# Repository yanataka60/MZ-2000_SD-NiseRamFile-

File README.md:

# MZ-2000_SD+偽RAMFILE複合ボード

しっぽいいんちょさんが作られた「偽RAMFILE for MZ-1500」を元にしてMZ-2000用にVRAM、GRAMのエミュレートの追加及びMZ-2000_SDと合体させたボードです。

以下の機能があります。

・MZ-2000_SDの起動及びMZ-2000_SDの機能

・EMM1からの起動(ただし、EMM1にHu-BASICの起動ディスクイメージがある場合のみ)

・MZ-2000のテキスト出力及びグラフィック出力をエミュレートしてVGA出力

・EMM1エミュレータ(320KByte)

・漢字ROMボードエミュレータ

・VGA出力される出力をI/Oポートの操作により機能強化(主にテキスト関連)

　　・キャラクタ単位でFONTの変更

　　・FONTキャラクタごとの色(前景色)及び背景色の指定

　　・すべてのキャラクタを1Dot単位で色指定可能なPCG

　　・FONTとPCGのプライオリティ設定

　　・テキストの色パレット機能

　　・グラフィックの色パレット機能

　　・テキストとグラフィックを色ごとにプライオリティ設定

MZ-2000_SD: https://github.com/yanataka60/MZ-2000_SD

#### アップロード済みのuf2ファイルでの正常動作が確認されました。当方ではSourceからの再ビルドにおいても問題は発生していません。
~~#### 2026.3.5追記 VGA出力はかなりシビアなタイミングになっています。グラフィックスを使いこなしたアクションゲームの中にはVGA出力が追いつかずに正常に表示されないものもあるようです。~~

## 回路図
　KiCadフォルダ内のMZ-2000_SD+NRF.pdfを参照してください。

[回路図](https://github.com/yanataka60/MZ-2000_SD-NiseRamFile-/blob/main/Kiacd/MZ-2000_SD%2BNRF.pdf)

|番号|品名|数量|備考|
| ------------ | ------------ | ------------ | ------------ |
|J2,J3|ピンソケット2x15Pin|2|RP2350Bマイコンボード用,秋月電子通商 FHU-2x42SGなど|
|J4|VGA用基板ソケット 3列15ピン|1|マルツ DJ-VGA14.5など (注1)|
||J5、J6のいずれか|||
|J5|Micro_SD_Card_Kit|1|秋月電子通商 AE-microSD-LLCNV (注2)|
|J6|MicroSD Card Adapter|1|Arduino等に使われる5V電源に対応したもの(注4)|
|U1|74LS04|1||
|U2|74LS30|1||
|U3|8255|1||
|U4|Arduino_Pro_Mini_5V|1|Atmega328版を使用 168版は不可。(注3)|
||RP2350Bボード(Raspberry Pi Pico 2)|1|Amazon WA00021 RP2350Bマイコンボードなど|
|C1-C3|積層セラミックコンデンサ 0.1uF|3||
|C4|電解コンデンサ 16v100uF|1||
|D1|ダイオード 1N5819|1||
|R1-R3|カーボン抵抗 330Ω|3||
||ピンヘッダ|2Pin分|Arduino_Pro_MiniにはA4、A5用のピンヘッダが付いていないため別途調達が必要です 秋月電子通商 PH-1x40SGなど|
||ピンソケット(任意)|26Pin分|Arduino_Pro_Miniを取り外し可能としたい場合に調達します 秋月電子通商 FHU-1x42SGなど|

　　　注1)VGA用基板ソケットには、ピン間隔の異なるものがあるようです。マルツ DJ-VGA14.5ではないものを購入する場合はこちらで寸法を確認してください。

　　　https://www.marutsu.co.jp/contents/shop/marutsu/datasheet/DJ-VGA14.5.pdf

　　　注2)秋月電子通商　AE-microSD-LLCNVのJ1ジャンパはショートしてください。

　　　注3)Arduino Pro MiniはA4、A5ピンも使っています。

　　　注4)MicroSD Card Adapterを使う場合

　　　　　J6に取り付けます。

MicroSD Card Adapterについているピンヘッダを除去してハンダ付けするのが一番確実ですが、J6の穴にMicroSD Card Adapterをぴったりと押しつけ、裏から多めにハンダを流し込むことでハンダ付けをする方法もあります。なお、この方法の時にはしっかりハンダ付けが出来たかテスターで導通を確認しておいた方が安心です。

ハンダ付けに自信のない方はJ5の秋月電子通商　AE-microSD-LLCNVをお使いください。AE-microSD-LLCNVならパワーLED、アクセスLEDが付いています。

## 偽RAMFILE for MZ-2000の書込み
　RP2350Bフォルダにあるniseramfile.uf2をRP2350Bマイコンボードに書き込みます。

　RP2350BのBOOTボタンを押しながらUSB-Cケーブルを接続するとパソコンがUSBメディアとして認識しますのでniseramfile.uf2をドロップすると自動的に書き込まれます。

　書き込みが終了するとパソコンからはUSBとして見えなくなりますのでそうなったらケーブルを抜いて終了です。

## MZ-2000_SD BOOT PROGRAMをMZ-1R12 SRAMメモリ 0番バックアップスロットへ書き込み
　MZ-2000_SDリポジトリEMMフォルダ内のBOOT_A_LOADER.binをMZ-1R12 SRAMメモリ 0番バックアップスロットへ書き込んでください。

https://github.com/yanataka60/MZ-2000_SD/blob/main/EMM/BOOT_A_LOADER.bin

　書き込みにはpicotool.exeが必要となります。以下のウェブページ右側の「Releases」からダウンロードできます。

https://github.com/raspberrypi/pico-sdk-tools

```
picotool.exe load -v -x BOOT_A_LOADER.bin  -t bin -o 0x10080000
```

　次にSDカードに「@BOOT-A MZ-2000.bin」を置きます。作成方法は、MZ-2000_SDを参照してください。

https://github.com/yanataka60/MZ-2000_SD?tab=readme-ov-file#boot-a-mz-xxxxbin%E3%82%92%E4%BD%9C%E6%88%90%E3%81%97%E3%81%A6sd-card%E3%81%AB%E4%BF%9D%E5%AD%98%E3%81%99%E3%82%8B

　また、EMM1に起動可能な内容(HuBASIC起動イメージ)があればEMMからの起動が可能です。

　EMMの内容をチェックしていないのでEMMが起動可能な内容(HuBASIC起動イメージ)でなかった場合には暴走しますのでご注意ください。

　EMMから起動するためには、MZ-2000_SDリポジトリEMMフォルダ内の「@BOOT-EMM1.MZT」をSDカードにコピーしておく必要があります。

　EMM1からの起動方法は、「/」キーとテンキーの「1」を同時に押しながら電源ON時又はIPLリセットすることで「EMM1」のHuBASICから起動させることが出来ます。

## FONTファイルの書込み
　VGA出力を有効とするためにはMZ-2000のフォントをRP2350Bに書き込む必要があります。

　MZ-2000はソフトウェア的にフォントを取り出すすべがありません。頑張って作ってください。

　私はオーナーズマニュアルのASCIIコード表を見ながら作成しました。

　書き込みはpicotoolを使います。

```
picotool.exe load -v -x font.rom  -t bin -o 0x1001f000
```

## Arduinoプログラム
　MZ-2000_SDを参照してください。

https://github.com/yanataka60/MZ-2000_SD?tab=readme-ov-file#arduino%E3%83%97%E3%83%AD%E3%82%B0%E3%83%A9%E3%83%A0-1

## 拡張機能の使い方
### MZ-2000_SDの起動
　MZ-2000_SDの起動方法と同じです。「/」キーを押しながら電源投入又はIPL RESETしてください。

### EMM1エミュレータ
　320KByteのEMM1として機能します。バッテリーバックアップ機能はなく、電源断で内容は消失します。

　ただし、バックアップ用のSlotが32個用意されているので電源断前にSlotに退避しておくことが可能です。

　また、Slot0の内容は電源投入又はIPL RESETした時にEMM1に自動的にコピーされるのであたかもバッテリーバックアップされていたかのような使い方が出来ます。

　EMMとSlotとのやり取りはI/Oポートから指示します。

#### SlotxxからEMM1への復帰
|アドレス|R/W|説明|
| ------------ | ------------ | ------------ |
|8Ch|W|指定したSlot番号(0～31)のSlotの内容をEMM1に復帰|

#### EMM1からSlotxxへの退避
|アドレス|R/W|説明|
| ------------ | ------------ | ------------ |
|8Dh|W|指定したSlot番号(0～31)のSlotへEMM1の内容を退避|

HuBASICからは以下のようになります。

```
OUT &H8C,0
```

```
OUT &H8D,0
```

　また、EMM1に起動可能な内容(HuBASIC起動イメージ)があればEMMからの起動が可能です。

　EMMの内容をチェックしていないのでEMMが起動可能な内容(HuBASIC起動イメージ)でなかった場合には暴走しますのでご注意ください。

　EMM1からの起動方法は、「/」キーとテンキーの「1」を同時に押しながら電源ON時又はIPLリセットすることで「EMM1」のHuBASICから起動させることが出来ます。

　EMM1へのHuBASIC起動ディスクイメージ作成は、DISK版HuBASICのUtilityからEMM1へのCOPY ALLで作ってください。

　また、Emulatorで作られたEMMイメージを登録する場合はpicotoolから以下のようにします。

```
picotool.exe load -v -x EMM_image.bin  -t bin -o 0x10280000
```

　MZ-1500_SD+NiseRamFileの様にEMMMENUも対応させたいと思います。

### 漢字・辞書ROM MZ-1R13
　漢字・辞書ROM MZ-1R13から抽出したデータを登録します。

　抽出にはGET1R13を使いました。

http://fukui.s17.xrea.com/retro/mz2080b/mzgetkrom.html

　出来上がったファイルをpicotoolで登録します。

```
picotool.exe load -v -x MZ_1R13_DIC.ROM -t bin -o 0x10040000
```

```
picotool.exe load -v -x MZ_1R13.ROM  -t bin -o 0x10020000
```

### FONT変更機能
一時的にFONTを変更することが出来ます。電源断又はIPL RESETで元に戻ります。以下VGA出力機能に関する設定は電源断又はIPL RESETですべて元に戻ります

キャラクタデータは1キャラクタ8Byteの普通のフォーマットです。

|アドレス|R/W|説明|
| ------------ | ------------ | ------------ |
|71h|W|データ書き込み:キャラクタコード+1|
|72h|W|キャラクタコード指定|

例)

```
OUT@$72,41:OUT@$71,$FF,OUT@$71,$FF,OUT@$71,$FF,OUT@$71,$FF,OUT@$71,$FF,OUT@$71,$FF,OUT@$71,$FF,OUT@$71,$FF
```
### FONTカラー設定
FONTのカラーを指定できます。上位4Bitがキャラクタ色(前景色)、下位4Bitが背景色になります。

|アドレス|R/W|説明|
| ------------ | ------------ | ------------ |
|79h|W|キャラクタ色(前景色)を上位4Bitで背景色を下位4Bitで指定する:キャラクタコード+1|
|7Ah|W|キャラクタコード指定|

例)キャラクタ「A」がGreenで表示されます。

```
OUT@$7A,41:OUT@$79,$40
```

### PCG定義
MZ-1500のPCGと同様の機能です。

1キャラクタ8Byteのキャラクタデータを3プレーン(合計24Byte)に書くことで1Dotごとに色指定が可能です。

|アドレス|R/W|説明|
| ------------ | ------------ | ------------ |
|61h|W|キャラクタコード指定|
|62h|W|書き込みバンク指定(Blue:1,Red:2,Green:3)|
|63h|W|データ書き込み:キャラクタコード+1|

### PCGの表示切替、FONTテキストとの優先順位変更
MZ-1500のPCGと同様の機能です。

Bit0でPCG表示の切り替え、Bit1でテキストとPCGの優先順位が変更できます。

|67h|W|Bit1 優先順位 0:テキスト文字色＞PCG＞テキスト背景色<br>　　　　　　1:PCG＞テキスト<br>Bit0 PCG表示  0:PCGを表示しない<br>　　　　　　1:PCGを表示する|

### テキストパレット設定
テキストの色について上位4Bitで表す色コードを下位4Bitで表す色に変えることが出来ます。

|アドレス|R/W|説明|
| ------------ | ------------ | ------------ |
|68h|W|上位4Bitで表す色コードを下位4Bitで表す色で表示する<br>　起動時設定<br>　　0x00<br>　　0x11<br>　　0x22<br>　　0x33<br>　　0x44<br>　　0x55<br>　　0x66<br>　　0x77|

例)起動時WhiteのテキストをGreenに変える

```
OUT@$68,$74
```

### グラフィックパレット設定
テキストの色とは別にグラフィックの色について上位4Bitで表す色コードを下位4Bitで表す色に変えることが出来ます。

|アドレス|R/W|説明|
| ------------ | ------------ | ------------ |
|69h|W|上位4Bitで表す色コードを下位4Bitで表す色で表示する<br>　起動時設定<br>　　0x00<br>　　0x11<br>　　0x22<br>　　0x33<br>　　0x44<br>　　0x55<br>　　0x66<br>　　0x77|

例)色指定7のグラフィックをGreenに変える

```
OUT@$69,$74
```

### グラフィックとテキストの優先順位変更
MZ-2000ではI/Oポート$F5によりテキストとグラフィックの優先順位を変更可能ですが、こちらを使うことで色ごとに優先順位を変更することが出来ます。

|アドレス|R/W|説明|
| ------------ | ------------ | ------------ |
|6Ah|W|上位4Bitで表す色コードを0Bitが1の時、グラフィック優先、0の時テキスト優先|

## MZ-80B、MZ-2500の80Bモードでの使用について
　MZ-2000_SD機能、EMM1エミュレータ、漢字ROMボードエミュレータはMZ-80B、MZ-2500の80Bモードでも問題なく動作しますが、VGA出力機能はVRAM、GRAMのアクセス方法がMZ-2000と異なるためまともな表示となりません。

## SAMPLE
### DEEP SCAN カラー化
　キャラクタに色を付けるサンプルプログラムを作ってみました。

　えむこまさんが公開されているMZ-80K/C版からの移植DEEP SCAN用に作ってみました。

https://github.com/mkomakonkon/MZ-2000/tree/master/IO/198005_DEEP_SCAN

　フォントファイルを入れ替える必要があるためEmuz-2200用とされていましたがMZ-2000_SD+偽RAMFILE複合ボードなら遊ぶことが出来ます。

　えむこまさんのサイトからダウンロードしたDEEP SCAN.zipを解凍するとFONT.ROMというファイルが含まれていますのでSampleフォルダのDEEP SCANフォルダにある「SET COLOR DEEP SCAN.mzt」の後ろにバイナリエディタなどでくっつけて一つのMZTファイルとします。

　また、DEEP SCANの実行ファイルであるDEEP SCAN.wavはDumpList Editorなどを使ってMZTファイル化してください。(実行アドレスを2000hに指定してMZTファイル化すると便利です)

　後はDEEP SCAN.MZTを実行する前にSET COLOR DEEP SCAN.mztを実行するだけです。

### グリーンモニター化
　カラーパレット機能を設定してキャラクタ、グラフィックともグリーン一色表示に変える「GREEN-MONITOR.mzt」をSampleフォルダのGREEN MONITORフォルダに置きました。

　MZ-2000_SD起動直後に実行すれば以降はグリーンモニターとなります。

　GVRAMを切り替えて表示するパラパラアニメ等にお使いください。

## おまけ
　グラフィックボードを装着していないMZ-2000でもVGA出力からカラーグラフィックが正常に利用できるバージョンを作ってみました。

　uf2ファイル

https://github.com/yanataka60/MZ-2000_SD-NiseRamFile-/blob/main/OMAKE/RP2350B/niseramfile_No_GVRAM.uf2

　ソースファイル

https://github.com/yanataka60/MZ-2000_SD-NiseRamFile-/tree/main/OMAKE/Source(No_GVRAM)

### 使用上の注意
　グラフィックボートが装着されていないこと。

　プレーン1のみのグラフィックボートが装着されている場合も取り外してください。

　MZ-2200もグラフィックボートを取り外せば使えます。

　MZ-80B、MZ-2500(80B、2000、2500モードとも)では正常に動作しません。通常のバージョンを使ってください。

## 開発環境、使用ライブラリなど
　開発環境は、Visual Studio Codeです。

　VGAライブラリは以下を使用しています。

- [VGA ライブラリ(一部改変)](https://github.com/vha3/Hunter-Adams-RP2040-Demos/tree/master/VGA_Graphics)

## 謝辞
　素晴らしい拡張モジュールを開発し、自由に改変・公開を快く承諾してくださったしっぽいいんちょさん、ありがとうございました。

## 追記
2026.3.5 kuran_kuran様よりkuran_kuran様作成ゲームでVGA出力が追いついていない事例の報告がありました。

2026.3.5 アップロード済みのuf2ファイルにおいては正常にVGA出力されることが確認されました。なお、niseramfile.cが$6Aポートの制御が抜けているファイルでしたので更新しました。

2026.3.6 使用ライブラリの記載を追加。

2026.3.6 Sampleプログラムを追加しました。

2026.3.7 開発環境を追記。

2026.3.16 おまけとしてNo_GVRAMバージョンを追加。

2026.3.27 Sampleフォルダに「GREEN-MONITOR.mzt」を追加。

2026.6.21 MZ-2000_SD+偽RAMFILE複合ボードに電源が供給されている状態でUSB-Cケーブルを接続してはいけない問題に対してすーぱーたーぼさんからご指摘いただいた対策を施しました。Rev1.0基板でも通常の使用でMZ-2000_SD+偽RAMFILE複合ボードに電源が供給されている状態でUSB-Cケーブルを接続することはありませんので通常使用においてRev1.0基板でも問題ありません。

2026.9.18 高速にEMMを読み出したときにエラーが発生するとkuran_kuranさんから指摘があり、RP2350Bのファームウェアについて提供された修正コードに差し替えました。

2026.10.13 80桁でグラフィックを画面全体に表示するとVGA出力の画面がブレてしまうとkuran_kuranさんから指摘があり、VGA処理の高速化を図りました。

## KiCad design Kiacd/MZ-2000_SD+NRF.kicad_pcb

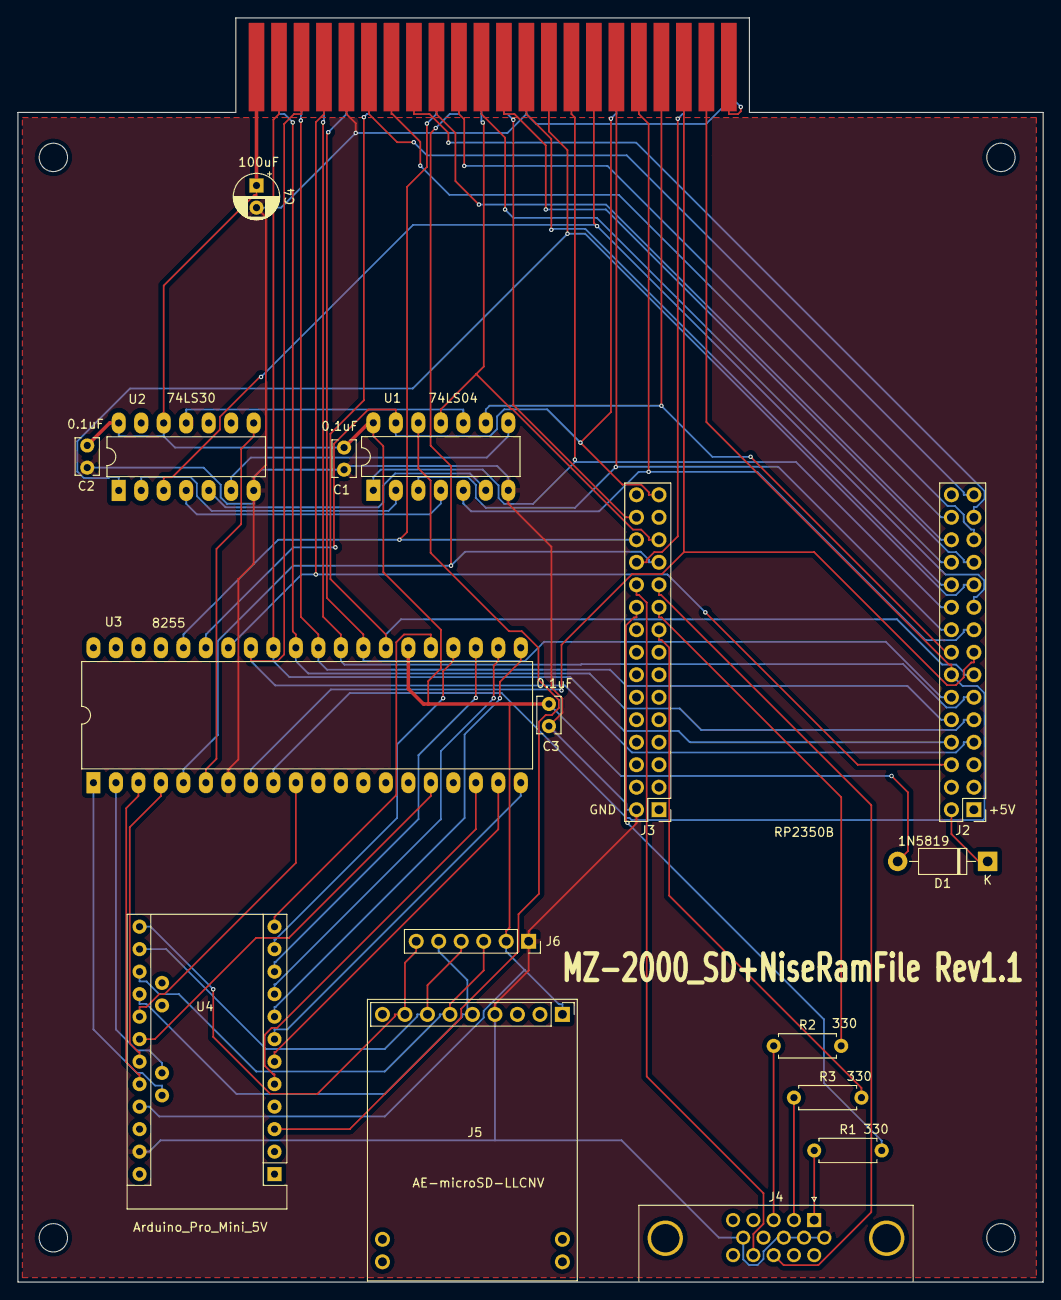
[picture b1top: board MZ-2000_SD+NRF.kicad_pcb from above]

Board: 2 copper layers, 115.8 x 142.7 mm, 22 parts (0 on the bottom side), 66 nets.

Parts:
C1, C2, C3: 0.1uF; C_Rect_L4.0mm_W2.5mm_P2.50mm
C4: 100uF; CP_Radial_D5.0mm_P2.50mm
D1: BAT54; D_DO-41_SOD81_P10.16mm_Horizontal
J1: Conn_02x22_Row_Letter_First; BUS_MZ2000
J2: RP2350B Left; PinHeader_2x15_P2.54mm_Vertical
J3: RP2350B Right; PinHeader_2x15_P2.54mm_Vertical
J4: VGA; DSUB-15-HD_Female_Horizontal_P2.29x1.98mm_EdgePinOffset3.03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
J5: Micro_SD_Card_Kit; AE-microSD-LLCNV
J6: MicroSD Card Adapter; PinSocket_1x06_P2.54mm_Vertical
MH1, MH2, MH3, MH4: MountingHole_3.2mm_M3
R1, R2, R3: 330; R_Axial_DIN0207_L6.3mm_D2.5mm_P7.62mm_Horizontal
U1: 74LS04; DIP-14_W7.62mm_LongPads
U2: 74LS30; DIP-14_W7.62mm_LongPads
U3: 8255; DIP-40_W15.24mm_LongPads
U4: Arduino_Pro_Mini_5V; Arduino_Pro_Mini

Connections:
+5V: C1.1, C2.1, C3.1, C4.1, D1.2, J1.a1, J1.b1, J5.1, J6.2, U1.14, U2.12, U2.14, U3.26, U4.21
/A0: J1.a21, J2.22, U3.9
/A1: J1.a20, J2.8, U3.8
/A2: J1.a19, J2.23, U1.9
/A3: J1.a18, J2.9, U1.5
/A4: J1.a17, J2.24, U1.3
/A5: J1.a16, J2.10, U2.3
/A6: J1.a15, J2.25, U1.1
/A7: J1.a14, J2.11, U2.1
/A8: J1.a13, J2.26
/A9: J1.a12, J2.12
/A10: J1.a11, J2.27
/A11: J1.a10, J2.13
/A12: J1.a9, J2.28
/A13: J1.a8, J2.14
/A14: J1.a7, J2.29
/A15: J1.a6, J2.15
/CS: J5.8, J6.6, U4.13
/D0: J1.a4, J2.18, U3.34
/D1: J1.a3, J2.4, U3.33
/D2: J1.a2, J2.19, U3.32
/D3: J1.b2, J2.5, U3.31
/D4: J1.b3, J2.20, U3.30
/D5: J1.b4, J2.6, U3.29
/D6: J1.b5, J2.21, U3.28
/D7: J1.b6, J2.7, U3.27
/MISO: J5.6, J6.3, U4.15
/MOSI: J5.7, J6.4, U4.14
/RESET: J1.b17, J3.15, U1.13, U3.35
/SCK: J5.5, J6.5, U4.16
/~EXWAIT: J1.b20, J3.27
/~IOREQ: J1.b11, J3.13, U1.11
/~MREQ: J1.b12, J3.29
/~RD: J1.b10, J3.12, U3.5
/~WR: J1.b9, J3.28, U3.36
GND: C1.2, C2.2, C3.2, C4.2, J1.a5, J1.a22, J1.b13, J1.b22, J3.16, J4.6, J4.7, J4.8, J4.10, J5.4, J6.1, U1.7, U2.7, U3.7, U4.23
unnamed: D1.1, J2.16
unnamed: J3.9, R3.2
unnamed: J3.10, R2.2
unnamed: J3.11, J4.13
unnamed: J3.25, R1.2
unnamed: J3.26, J4.14
unnamed: J4.1, R1.1
unnamed: J4.2, R3.1
unnamed: J4.3, R2.1
unnamed: U1.2, U2.2
unnamed: U1.4, U2.4
unnamed: U1.6, U2.5
unnamed: U1.8, U2.6
unnamed: U1.10, U2.11
unnamed: U1.12, U4.3
unnamed: U2.8, U3.6
unnamed: U3.1, U4.A5
unnamed: U3.2, U4.A4
unnamed: U3.3, U4.20
unnamed: U3.4, U4.19
unnamed: U3.10, U4.17
unnamed: U3.16, U4.18
unnamed: U3.18, U4.5
unnamed: U3.19, U4.6
unnamed: U3.20, U4.7
unnamed: U3.21, U4.8
unnamed: U3.22, U4.9
unnamed: U3.23, U4.10
unnamed: U3.24, U4.11
unnamed: U3.25, U4.12

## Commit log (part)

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2026-03-04 Create Source
2026-03-16 Create OMAKE
